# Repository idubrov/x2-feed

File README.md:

# x2-feed

Stepper-motor based power feed for X2 mill.

The following features are supported:

1. Power feeding in both directions.
1. Two feed modes: "slow" and "fast".
1. Setting feed speed via rotary encoder (both "slow" and "fast").
1. Spindle tachometer via hall sensor.
1. Emergency stop mode: halts stepper motor driver when emergency stop is pressed.
1. LCD screen displays current spindle speed and feed speed.

## PCB
See PCB (Eagle CAD) in the [pcb/](pcb/) directory.

## Building

You need the following software installed:

1. [Rust](https://www.rust-lang.org) 
1. [xargo](https://github.com/japaric/xargo)

To build the binary, run `xargo build`.

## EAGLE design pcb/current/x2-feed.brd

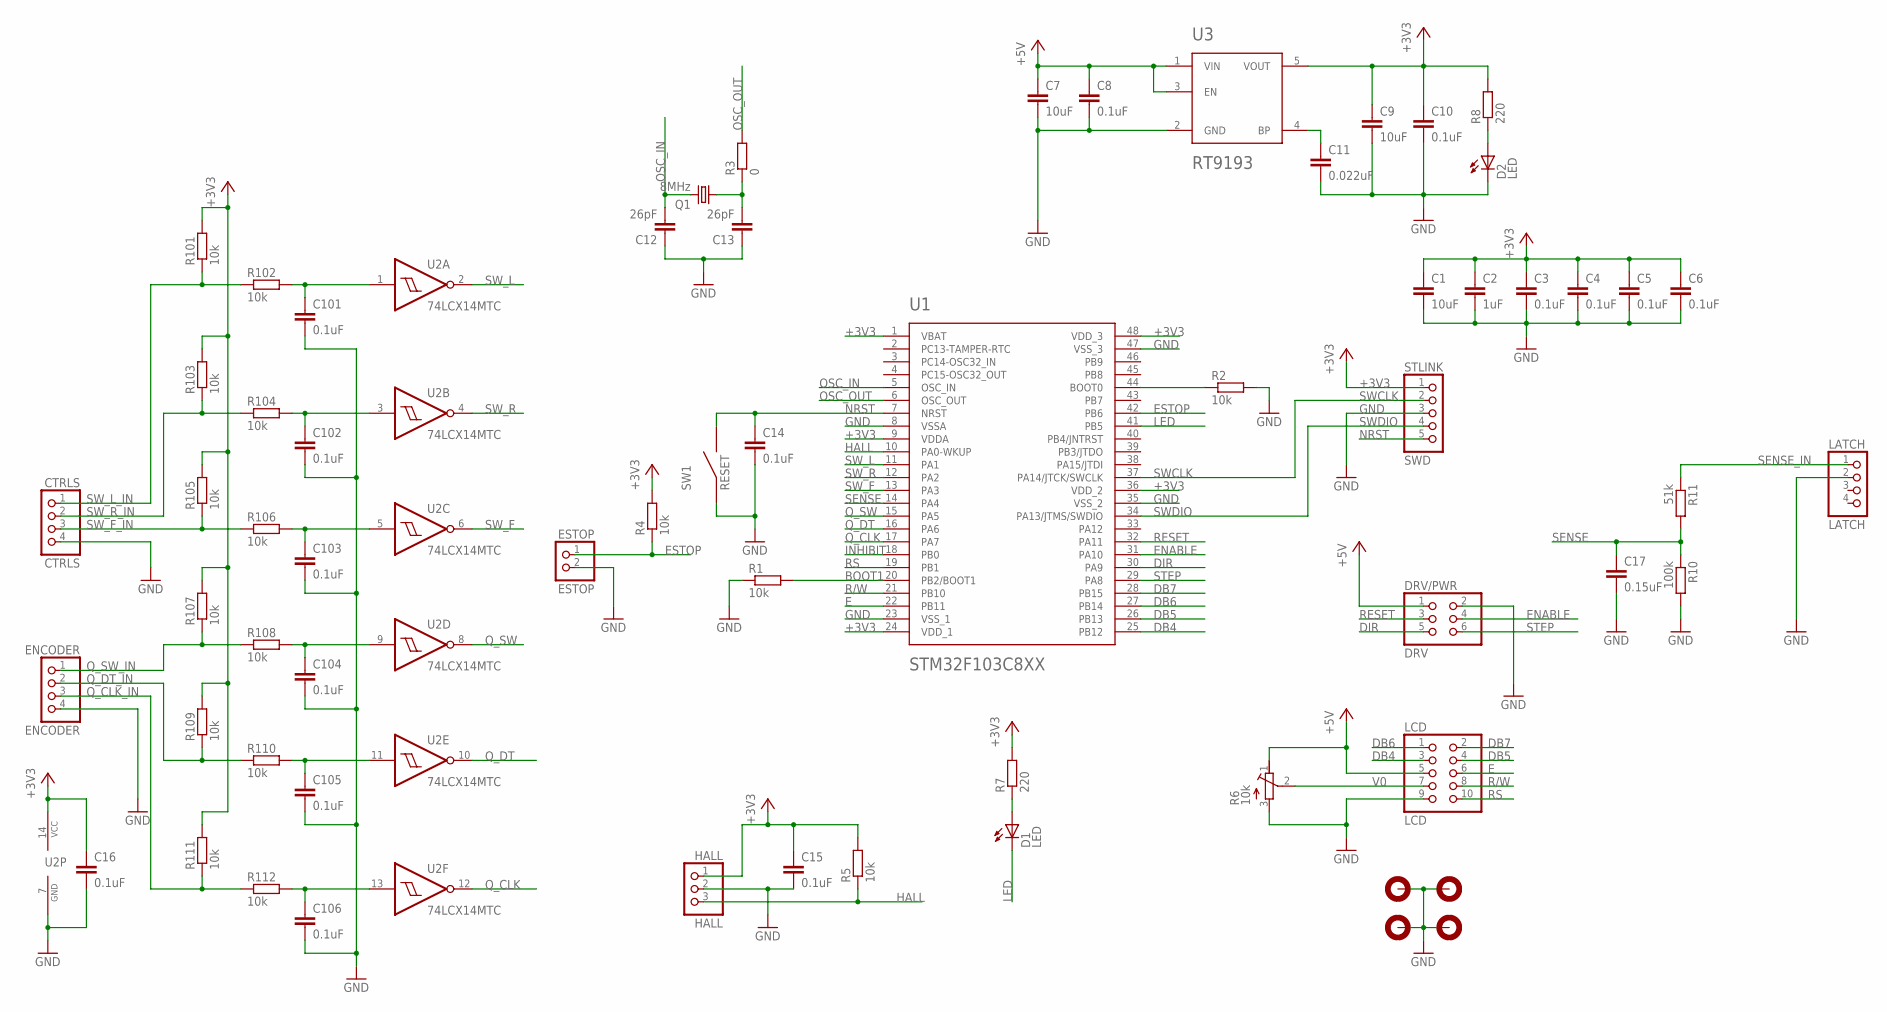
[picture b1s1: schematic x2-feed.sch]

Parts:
C1, C7, C9: 10uF; C2012
C2: 1uF; C1608
C3, C4, C5, C6, C8, C10, C14, C15, C16, C101, C102, C103, C104, C105, C106: 0.1uF; C1608
C11: 0.022uF; C1608
C12, C13: 26pF; C1608
C17: 0.15uF; C1608
CTRLS: CTRLS; 1X04
D1, D2: LED; LED2012
DRV/PWR: DRV; 2X03
ENCODER: ENCODER; 1X04
ESTOP: ESTOP; 1X02
H1, H2, H3, H4: MOUNT-PAD-ROUND2.8; 2,8-PAD
HALL: HALL; 5-103361-1
LATCH: LATCH; 1X04
LCD: LCD; 2X05
Q1: 8MHz; HC49/S
R1, R2, R4, R5, R101, R102, R103, R104, R105, R106, R107, R108, R109, R110, R111, R112: 10k; R1608
R3: 0; R1608
R6: 10k; RTRIMT93YA
R7, R8: 220; R1608
R10: 100k; R1608
R11: 51k; R1608
STLINK: SWD; 1X05
SW1: RESET; PUSH
U1: STM32F103C8XX; LQFP48-7X7MM
U2: 74LCX14MTC; TSSOP14
U3: RT9193; SOT23-5L

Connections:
+3V3: C1.1, C2.1, C3.1, C4.1, C5.1, C6.1, C9.1, C10.1, C15.1, C16.1, HALL.1, R4.2, R5.2, R7.2, R8.2, R101.2, R103.2, R105.2, R107.2, R109.2, R111.2, STLINK.1, U1.1 (VBAT), U1.9 (VDDA), U1.24 (VDD_1), U1.36 (VDD_2), U1.48 (VDD_3), U2.14 (VCC), U3.5 (VOUT)
+5V: C7.1, C8.1, DRV/PWR.1, LCD.5, R6.1 (E), U3.1 (VIN), U3.3 (EN)
BOOT0: R2.1, U1.44 (BOOT0)
BOOT1: R1.2, U1.20 (PB2/BOOT1)
BP: C11.1, U3.4 (BP)
DB4: LCD.3, U1.25 (PB12)
DB5: LCD.4, U1.26 (PB13)
DB6: LCD.1, U1.27 (PB14)
DB7: LCD.2, U1.28 (PB15)
DIR: DRV/PWR.5, U1.30 (PA9)
E: LCD.6, U1.22 (PB11)
ENABLE: DRV/PWR.4, U1.31 (PA10)
ESTOP: ESTOP.1, R4.1, U1.42 (PB6)
GND: C1.2, C2.2, C3.2, C4.2, C5.2, C6.2, C7.2, C8.2, C9.2, C10.2, C11.2, C12.1, C13.1, C14.2, C15.2, C16.2, C17.2, C101.2, C102.2, C103.2, C104.2, C105.2, C106.2, CTRLS.4, D2.C, DRV/PWR.2, ENCODER.4, ESTOP.2, H1.B2,8, H2.B2,8, H3.B2,8, H4.B2,8, HALL.2, LATCH.2, LCD.9, R1.1, R2.2, R6.3 (A), R10.2, STLINK.3, SW1.1, SW1.2 (1), U1.8 (VSSA), U1.23 (VSS_1), U1.35 (VSS_2), U1.47 (VSS_3), U2.7 (GND), U3.2 (GND)
HALL: HALL.3, R5.1, U1.10 (PA0-WKUP)
INHIBIT: U1.18 (PB0)
LED: D1.C, U1.41 (PB5)
unnamed: C13.2, Q1.1, R3.1
unnamed: D1.A, R7.1
unnamed: C101.1, R102.2, U2.1 (I)
unnamed: D2.A, R8.1
unnamed: C102.1, R104.2, U2.3 (I)
unnamed: C103.1, R106.2, U2.5 (I)
unnamed: C104.1, R108.2, U2.9 (I)
unnamed: C105.1, R110.2, U2.11 (I)
unnamed: C106.1, R112.2, U2.13 (I)
NRST: C14.1, STLINK.5, SW1.3 (2), SW1.4 (2), U1.7 (NRST)
OSC_IN: C12.2, Q1.2, U1.5 (OSC_IN)
OSC_OUT: R3.2, U1.6 (OSC_OUT)
Q_CLK: U1.17 (PA7), U2.12 (O)
Q_CLK_IN: ENCODER.3, R111.1, R112.1
Q_DT: U1.16 (PA6), U2.10 (O)
Q_DT_IN: ENCODER.2, R109.1, R110.1
Q_SW: U1.15 (PA5), U2.8 (O)
Q_SW_IN: ENCODER.1, R107.1, R108.1
R/W: LCD.8, U1.21 (PB10)
RESET: DRV/PWR.3, U1.32 (PA11)
RS: LCD.10, U1.19 (PB1)
SENSE: C17.1, R10.1, R11.2, U1.14 (PA4)
SENSE_IN: LATCH.1, R11.1
STEP: DRV/PWR.6, U1.29 (PA8)
SWCLK: STLINK.2, U1.37 (PA14/JTCK/SWCLK)
SWDIO: STLINK.4, U1.34 (PA13/JTMS/SWDIO)
SW_F: U1.13 (PA3), U2.6 (O)
SW_F_IN: CTRLS.3, R105.1, R106.1
SW_L: U1.11 (PA1), U2.2 (O)
SW_L_IN: CTRLS.1, R101.1, R102.1
SW_R: U1.12 (PA2), U2.4 (O)
SW_R_IN: CTRLS.2, R103.1, R104.1
V0: LCD.7, R6.2 (S)

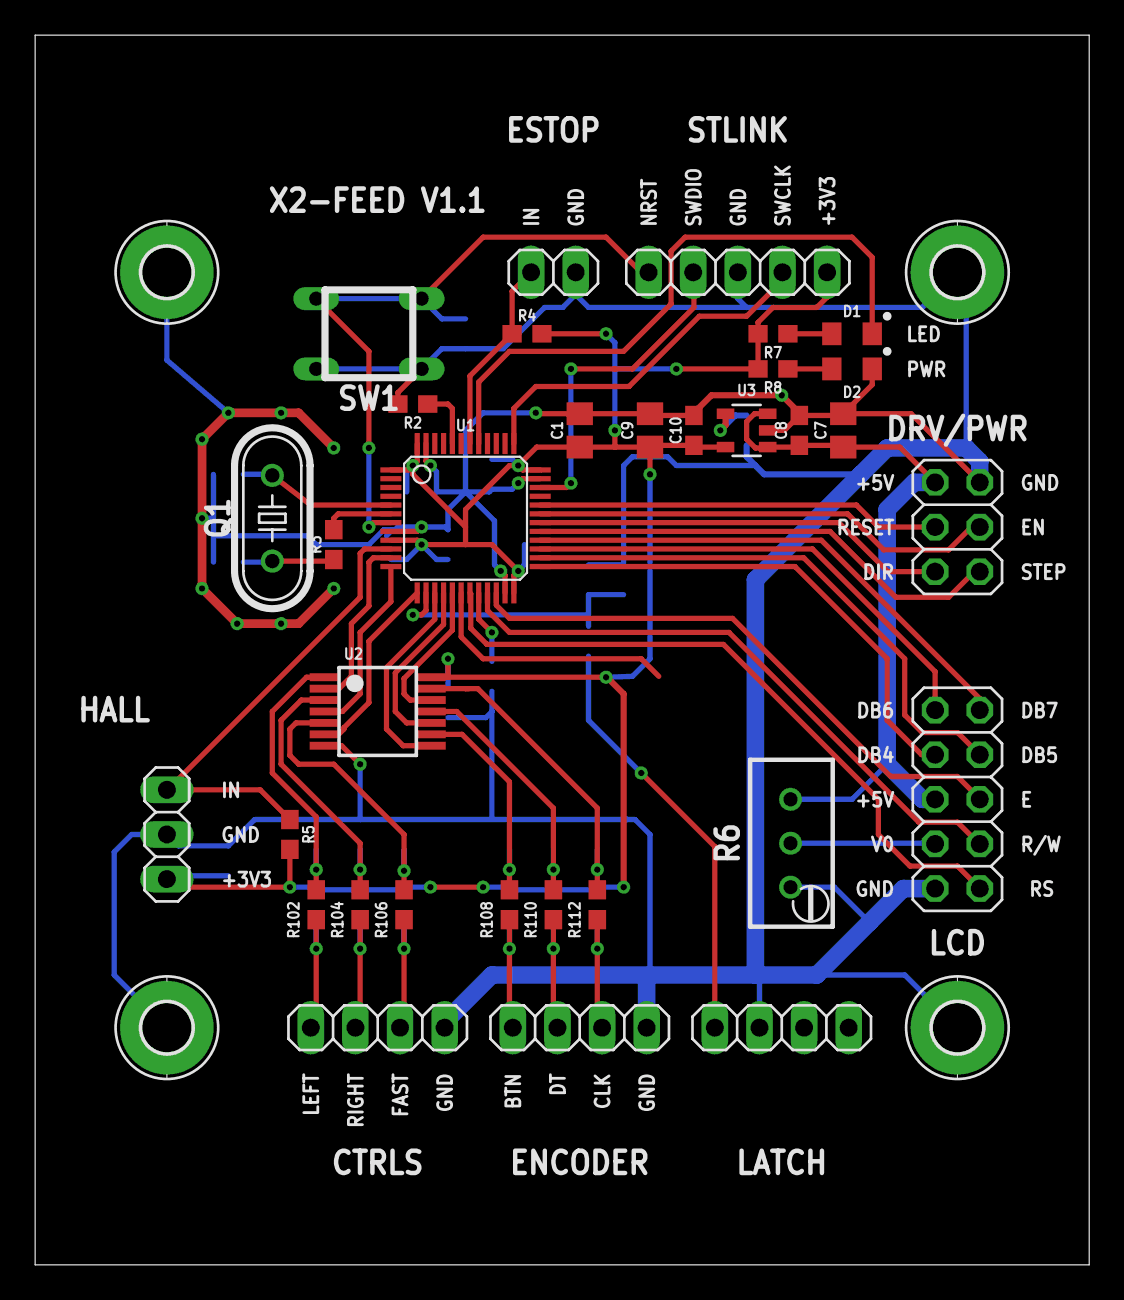
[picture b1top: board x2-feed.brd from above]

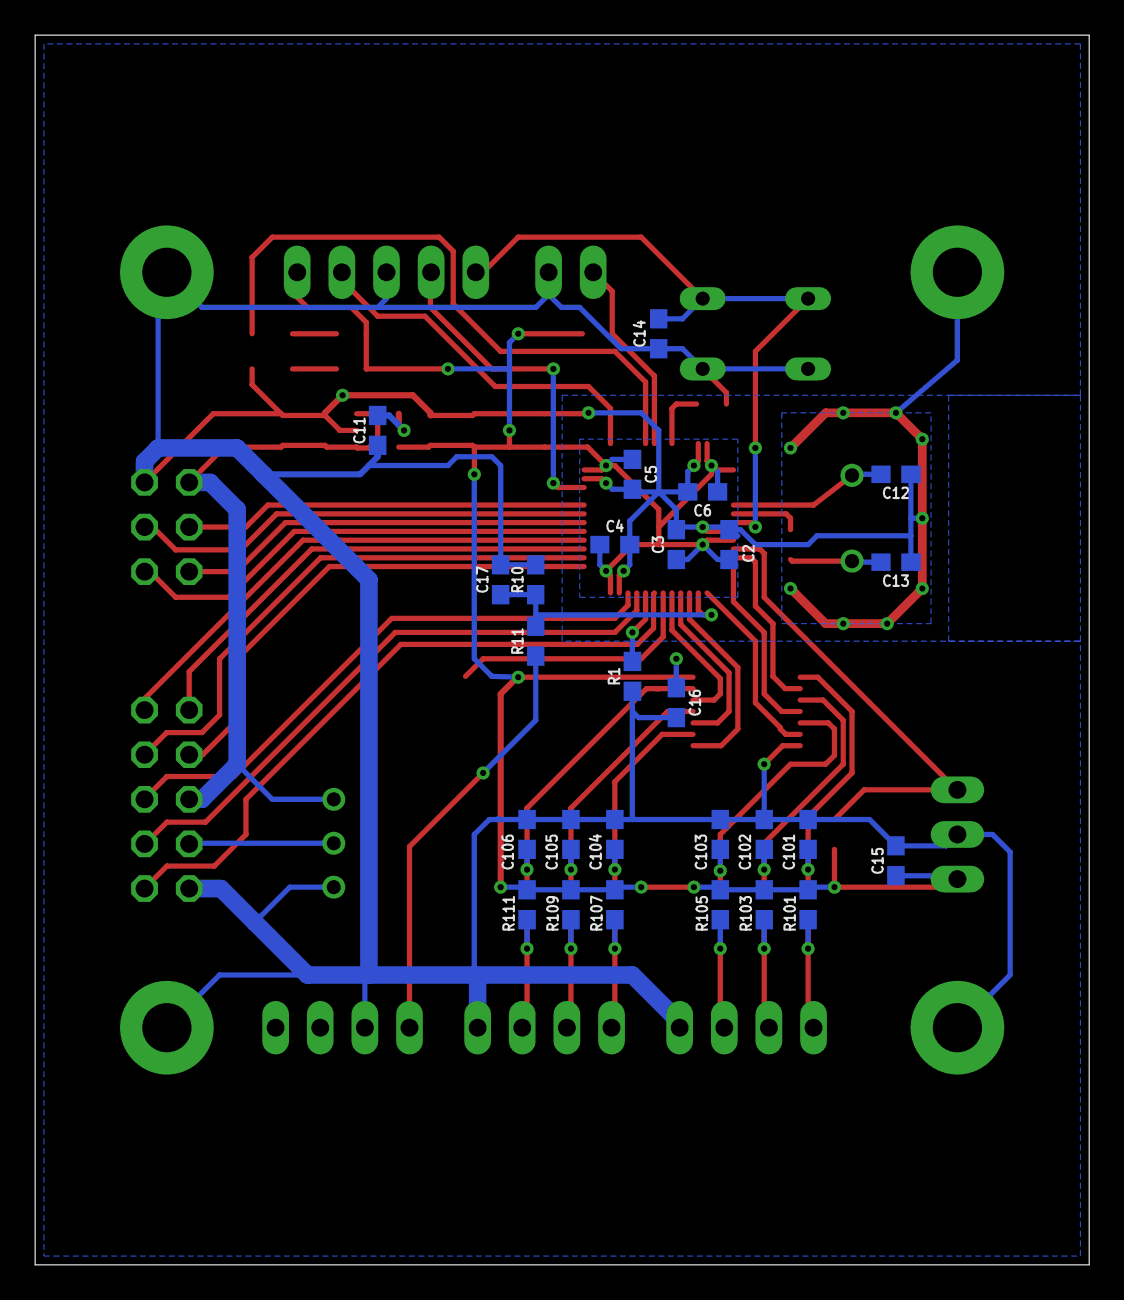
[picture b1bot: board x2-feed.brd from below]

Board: 2 copper layers, 60.0 x 70.0 mm, 64 parts (27 on the bottom side), 49 nets.

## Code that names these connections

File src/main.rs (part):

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//! 1. Power feeding in both directions.
//! 1. Two feed modes: "slow" and "fast".
//! 1. Setting feed speed via rotary encoder (both "slow" and "fast").
//! 1. Spindle tachometer via hall sensor.
//! 1. Emergency stop mode: halts stepper motor driver when emergency stop is pressed.
//! 1. Screen screen displays current spindle speed and feed speed.
//!
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        core.SYST.set_reload(0x00ff_ffff);

        let mut gpioa = peripherals.GPIOA.split();
        let hall_pin = gpioa.pa0.into_pull_up_input(&mut gpioa.crl);
        let left_btn = gpioa.pa1.erase();
        let right_btn = gpioa.pa2.erase();
        let fast_btn = gpioa.pa3.erase();
        let led_pin = gpioa.pa4.into_push_pull_output(&mut gpioa.crl).erase();
        let encoder_btn = gpioa.pa5.erase();
        let encoder_dt_pin = gpioa.pa6;
        let encoder_clk_pin = gpioa.pa7;
        let step_pin = gpioa.pa8.into_alternate_open_drain(&mut gpioa.crh);
        let dir_pin = gpioa.pa9.into_open_drain_output(&mut gpioa.crh).erase();
        let enable_pin = gpioa.pa10.into_open_drain_output(&mut gpioa.crh).erase();
        let reset_pin = gpioa.pa11.into_open_drain_output(&mut gpioa.crh).erase();

        // "Passivate" unused pins (pull them down), to avoid them floating with noise.
        gpioa.pa12.into_pull_down_input(&mut gpioa.crh);
        // Used by debugger, no need to "passivate"
        //gpioa.pa13.into_pull_down_input(&mut gpioa.crh);
        //gpioa.pa14.into_pull_down_input(&mut gpioa.crh);
        //gpioa.pa15.into_pull_down_input(&mut gpioa.crh);

        let mut gpiob = peripherals.GPIOB.split();
        let rs_pin = gpiob.pb1.into_push_pull_output(&mut gpiob.crl).erase();
        let rw_pin = gpiob.pb10.into_push_pull_output(&mut gpiob.crh).erase();
        let e_pin = gpiob.pb11.into_push_pull_output(&mut gpiob.crh).erase();
        let db4 = gpiob.pb12.into_push_pull_output(&mut gpiob.crh).erase();
        let db5 = gpiob.pb13.into_push_pull_output(&mut gpiob.crh).erase();
        let db6 = gpiob.pb14.into_push_pull_output(&mut gpiob.crh).erase();
        let db7 = gpiob.pb15.into_push_pull_output(&mut gpiob.crh).erase();

        // "Passivate" unused pins (pull them down), to avoid them floating with noise.
        gpiob.pb2.into_pull_down_input(&mut gpiob.crl);
        // Used by debugger, no need to "passivate"
        //gpiob.pb3.into_pull_down_input(&mut gpiob.crl);
        //gpiob.pb4.into_pull_down_input(&mut gpiob.crl);
        gpiob.pb5.into_pull_down_input(&mut gpiob.crl);
        gpiob.pb6.into_pull_down_input(&mut gpiob.crl);
        gpiob.pb7.into_pull_down_input(&mut gpiob.crl);
        gpiob.pb8.into_pull_down_input(&mut gpiob.crh);
        gpiob.pb9.into_pull_down_input(&mut gpiob.crh);
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        let led = Led::new(led_pin);
        let screen = Screen::new(rs_pin, rw_pin, e_pin, [db4, db5, db6, db7]);
        let encoder = QuadEncoder::new(peripherals.TIM3, encoder_dt_pin, encoder_clk_pin);
        let hall = RpmSensor::new(peripherals.TIM2, hall_pin);
        let is_lathe = crate::settings::IS_LATHE.read(&mut flash) != 0;
        let stepper = Stepper::new(DRIVER_TICK_FREQUENCY, driver, !is_lathe);
        let mut display = Display::new(screen);
        let controls = Controls::new(left_btn, right_btn, fast_btn, encoder_btn);

        // Pull-up e-stop (it's `1` when not active).
        let estop = EStop::new(gpiob.pb0.into_pull_up_input(&mut gpiob.crl).erase());

        // LCD device init
        // Need to wait at least 40ms after Vcc rises to 2.7V
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pub fn begin_panic_handler(info: &PanicInfo<'_>) -> ! {
    // Immediately disable driver outputs, just in case
    let mut gpioa = unsafe { Peripherals::steal().GPIOA }.split();
    gpioa.pa10.into_push_pull_output(&mut gpioa.crh).set_low();

    // Steal GPIOB and create another screen in an attempt to print some info
    let mut gpiob = unsafe { Peripherals::steal().GPIOB }.split();
    let rs_pin = gpiob.pb1.into_push_pull_output(&mut gpiob.crl).erase();
    let rw_pin = gpiob.pb10.into_push_pull_output(&mut gpiob.crh).erase();
    let e_pin = gpiob.pb11.into_push_pull_output(&mut gpiob.crh).erase();
    let db4 = gpiob.pb12.into_push_pull_output(&mut gpiob.crh).erase();
    let db5 = gpiob.pb13.into_push_pull_output(&mut gpiob.crh).erase();
    let db6 = gpiob.pb14.into_push_pull_output(&mut gpiob.crh).erase();
    let db7 = gpiob.pb15.into_push_pull_output(&mut gpiob.crh).erase();

    let screen = Screen::new(rs_pin, rw_pin, e_pin, [db4, db5, db6, db7]);
    let mut display = Display::new(screen);
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
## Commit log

2017-05-25 Initial version of X2 PowerFeed and Motor Control
2017-05-27 LCD screen added
2017-05-27 Creating 'hw' module to contain all hardware-specific stuff
2017-05-27 Adding support for rotary encoder
2017-05-29 Started working on driver
2017-05-29 Working on driver
2017-05-29 Working on powerfeed
2017-05-29 Implementing power feed algorithm
2017-05-29 Refactorings
    * Extracting controls into separate module
    * Removing delays for direction setup/hold (for IM483 these are around one CPU instruction anyway)
2017-05-30 Adding RPM sensor support
    * Hall-sensor based tachometer
2017-05-30 Minor refactorings
2017-05-30 Fixing off-by-one error
2017-05-30 Fixing deadlock situation
    When checking if driver is stopped, don't wait for update flag to reset.
    This operation is currently only called when update interrupt is disabled,
    so it will never reset.
2017-05-30 Minor tweaks
2017-05-31 Error handling
2017-06-01 Using core::fmt
2017-06-04 Updating README
2017-06-04 Updating dependencies
    Updating to use crates from the remote repository.
2017-06-04 Updating to use dependencies from git
2017-06-06 Pull down unused ports
2017-06-06 Changing formatting of IPM/RPM
    Also, fixing bug in hall.rs.
2017-06-06 Starting 0.1.1-pre
2017-07-30 Porting to new version of RTFM (0.2.1)
2017-09-09 Updating packages versions
2017-09-09 Fixing warnings when using latest nightly Rust
2017-09-09 Tagging version 0.2.0
2017-09-09 CircleCI build
2017-09-09 Making build verbose on CircleCI
2017-09-09 Don't override https github URL with git+ssh
2017-09-10 Code clenup, checking code with clippy
2017-09-10 Minor cleanup + run clippy on CircleCI
2017-09-10 Install clippy before checking out the project
2017-09-10 Show feed direction
2017-09-11 Using stepgen and lcd from crates.io
2017-09-11 Minor cleanup
    Using `bool` to indicate no step was loaded
2017-09-12 Updating for the latest
2017-09-12 Don't use unsafe to read controls
    For consistency, use safe access to GPIOA
2017-09-12 Added FIXME
2017-09-12 Clippy is in docker image already
2017-09-12 Use git dependency
2017-09-12 Minor comment tweak
2017-09-14 Updating stepgen dependency version
2017-09-14 Updating to lcd 0.2.0
2017-09-19 Minor code simplification
2017-09-19 Started HAL layer refactoring
2017-09-19 Continuing HAL refactoring
    * Encoder, controls and led.
2017-09-19 Starting heavy refactoring of stepper/driver
    Trying to separate `hw` module from `hal` module. `hal` is for
    interfaces to the hardware whereas `hw` is for bindings to the
    concrete hardware.
2017-09-19 Working on better separation between step controller and stepper driver
2017-09-20 Continuing refactoring HW/HAL
2017-09-20 Refactoring hall sensor and quad encoder
2017-09-20 Futher refactoring
2017-09-20 Setting priorities
2017-09-26 Experimenting with TIM4 slave mode
2017-09-26 Converting screen to use stm32-extras
    Also, changing timer not to change SYST register
2017-09-26 Fixing clippy errors; minor doc update
2017-09-26 Converting controls to stm32-extras
2017-09-26 Cleaning up the code
2017-09-26 Allow dead code for now
2017-09-26 Another attempt at better hardware
2017-09-26 Refactoring screen
2017-09-26 Finishing refactoring for hardware-related code
2017-09-27 Using bitband API
2017-09-27 Fixing dependency; minor tweaks
2017-09-27 Fixing clippy error
2017-09-30 Started working on menu system
    Also, updating for the latest stm32-hal module and adding support for EEPROM.
2017-09-30 Starting working on a new menu
2017-09-30 Working on better controls handling
2017-09-30 Fixing clippy warning
2017-09-30 Rewriting feed to use controls events
2017-09-30 Reworking stepper state a little
2017-10-01 Custom panic function; don't capture driver when not needed
2017-10-01 Removing trait RpmSensor
2017-10-01 Fixing panic func
2017-10-01 Working on menu
2017-10-01 Fixing clippy warning; minor comment tweak
2017-10-24 Working on settings
2017-10-24 Loading settings on feed
2017-10-24 IPR feeds
2017-10-24 Minor style changes
2017-10-24 Acceleration setting
2017-10-25 Print error on panic
2017-10-25 Better handling of slow/fast errors; fixing overflow bug
2017-10-25 Handle stepgen errors; different exit condition
    Making long pressing of encoder to be an exit condition from the menu.
2017-10-25 Using git dependency
2017-10-25 Fixing clippy warnings
2017-10-25 Changing the way back/exit works
2017-10-25 Started working on limits; fixing error handling in stepper a little
2017-10-26 Working on limits support
    * Generalizing navigation a little
    * Adding two submenus to capture feed limits (left and right)
2017-10-26 Fixing bugs
    * Fixing navigation in feed
    * Fixing stepper not setting state to stopped when going to given position
    * Setting traversal speed when setting limits
2017-10-26 Removing one extra state from stepper
2017-10-26 Refactoring stepper
2017-10-26 Cleaning up stepper code
2017-10-26 Make EEPROM area smaller
2017-10-26 Don't require Display
2017-10-26 Minor cleanups
2021-12-29 Porting code to latest stable Rust and latest embedded crates
    Also, bringing in external crates into the workspace for convenience.
2021-12-29 Cleanup
2021-12-29 Working on thread cutting
2021-12-30 Temp
2021-12-30 Fixing issues
2021-12-31 Some refactorings
    Removing macroses from menus, reimplement them manually. Simplify
    menus.
    Adding `#[inline(never)]` to LCD implementation as those functions
    generally take long to finish anyways and there is no reason to inline
    them (which makes code larger).
2021-12-31 More refactorings
2022-01-01 Minor fixes
2022-01-02 switching to HAL
2022-01-02 Switching encoder to use 4 ticks per step
    Switching encoder to use 4 ticks per step instead of 2 so we can
    have a bit of hysteresis action.
2022-01-02 Switching to STM32F1XX hal
2022-01-03 Some cleanup and refactoring
2022-01-03 Converting to HAL; fixing issue with encoder
2022-01-03 Some cleanup
2022-01-03 Removing our own HAL for flash
2022-01-03 formatting
2022-01-03 More flash / eeprom work
2022-01-04 Switching back to external crates; github action
2022-01-04 Use different target
2022-01-04 cargo fmt
2022-08-04 Another TPI
2022-08-04 Clippy fix
2022-11-19 Bumping dependencies
2022-11-19 Clippy
